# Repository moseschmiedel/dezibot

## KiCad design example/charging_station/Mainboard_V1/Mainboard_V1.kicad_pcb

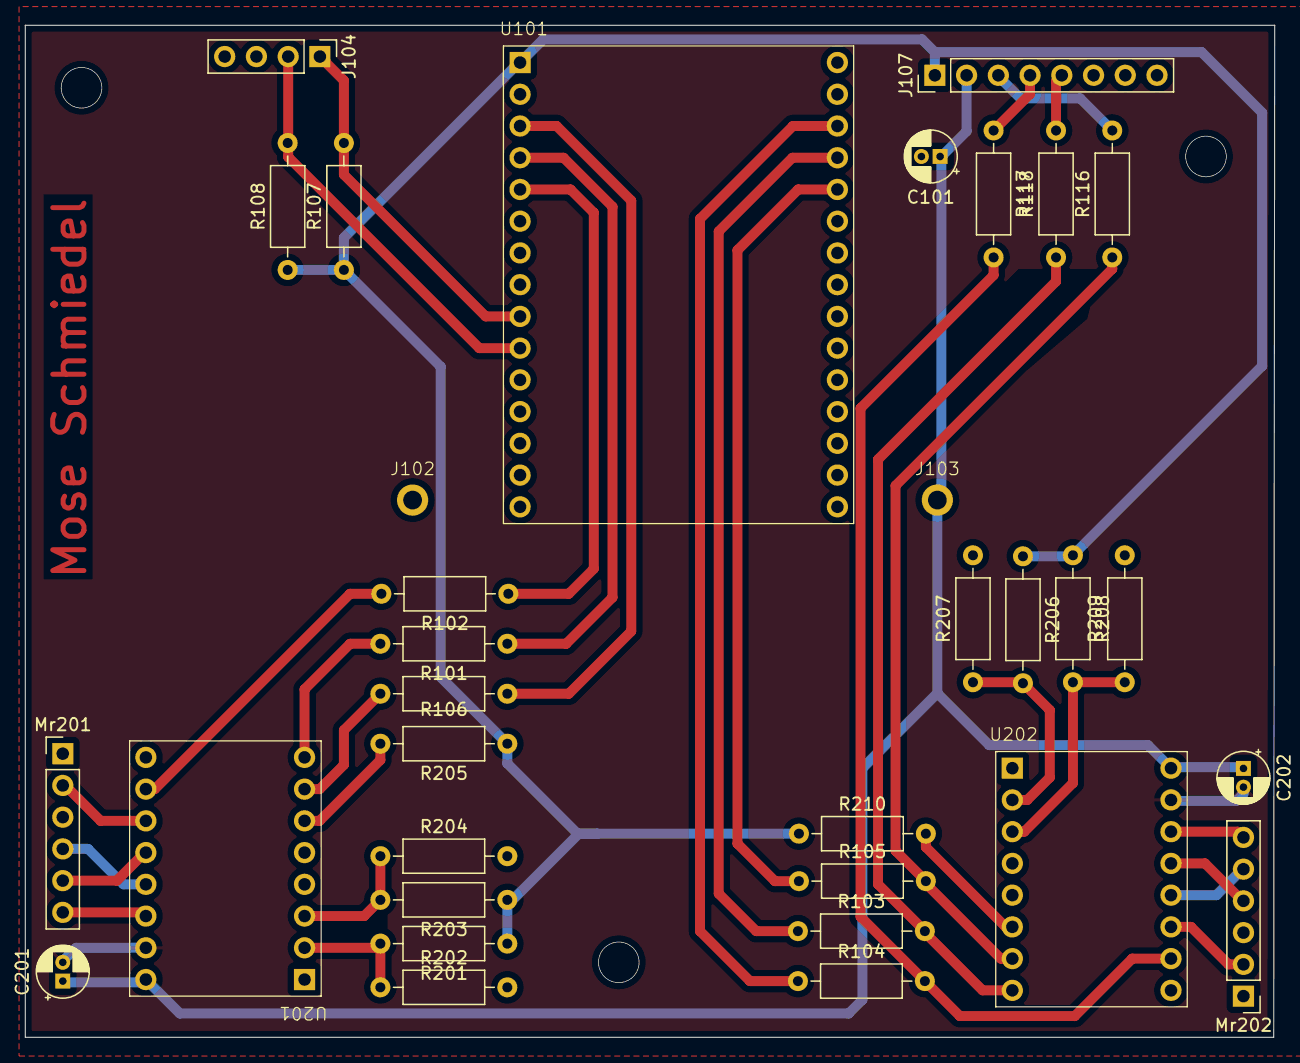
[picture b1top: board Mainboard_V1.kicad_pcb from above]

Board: 2 copper layers, 100.0 x 81.0 mm, 33 parts (0 on the bottom side), 34 nets.

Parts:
C101, C201, C202: 100uF; CP_Radial_D4.0mm_P1.50mm
J102, J103: PogoPin
J104: Conn_01x04_Pin; PinHeader_1x04_P2.54mm_Vertical
J107: Conn_01x08_Pin; PinHeader_1x08_P2.54mm_Vertical
Mr201, Mr202: Stepper_Motor_unipolar_6pin; PinHeader_1x06_P2.54mm_Vertical
R101, R102, R103, R104, R105, R106, R107, R108, R116, R117, R118, R201, R202, R203, R204, R205, R206, R207, R208, R209, R210: 1k; R_Axial_DIN0207_L6.3mm_D2.5mm_P10.16mm_Horizontal
U101: ESP32-WROOM-32; diymore-ESP32-WROOM-32-Devboard
U201, U202: DRV8834; Polulu_DRV8834

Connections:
/DIR_LEFT: R101.2, U201.8 (DIR)
/DIR_RIGHT: R103.2, R118.1, U202.8 (DIR)
/SCL: J104.2, R108.2, U101.10 (D19)
/SDA: J104.1, R107.2, U101.9 (D18)
/STEP_LEFT: R106.2, U201.7 (STEP)
/STEP_RIGHT: R105.2, R116.1, U202.7 (STEP)
/Stepper Motors/~SLEEP_LEFT: R205.2, U201.6 (~SLEEP)
/Stepper Motors/~SLEEP_RIGHT: R210.2, U202.6 (~SLEEP)
/~FAULT_LEFT: R102.2, U201.15 (~FAULT)
/~FAULT_RIGHT: R104.2, R117.2, U202.15 (~FAULT)
GND: C201.2, C202.2, U201.10 (GND), U202.10 (GND)
unnamed: J107.3, R116.2
unnamed: J107.4, R117.1
unnamed: J107.5, R118.2
unnamed: Mr201.5 (-), U201.13 (A1)
unnamed: R101.1, U101.4 (D2)
unnamed: R102.1, U101.5 (D4)
unnamed: R103.1, U101.19 (D12)
unnamed: R104.1, U101.18 (D13)
unnamed: R105.1, U101.20 (D14)
unnamed: R106.1, U101.3 (D15)
unnamed: Mr201.2, U201.14 (A2)
unnamed: Mr201.4, U201.12 (B1)
unnamed: Mr201.6, U201.11 (B2)
unnamed: R201.2, R202.1, U201.2 (M0)
unnamed: R203.2, R204.1, U201.3 (M1)
unnamed: Mr202.5 (-), U202.13 (A1)
unnamed: Mr202.2, U202.14 (A2)
unnamed: Mr202.4 (-), U202.12 (B1)
unnamed: Mr202.6, U202.11 (B2)
unnamed: R206.2, R207.1, U202.2 (M0)
unnamed: R208.2, R209.1, U202.3 (M1)
VBUS: C101.1, C201.1, C202.1, J103.1, J107.2, U201.9 (VMOT), U202.9 (VMOT)
VDD: J107.1, R107.1, R108.1, R201.1, R203.1, R205.1, R206.1, R208.1, R210.1, U101.1 (3V3)

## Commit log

2024-10-29 Add directory structure for charging_station firmware
2025-03-05 autocharge/#10-pick: specify `AbstractSet`
2025-03-05 autocharge/#10-pick: implement `AbstractSet` with `Fifo`
2025-03-05 autocharge/#10-pick: add `Master`
2025-03-05 autocharge/#10-pick: add `Slave`
2025-03-06 autocharge/#10-pick: add cs state `SLAVE_CHARGE`
2025-03-06 autocharge/#9-communication: specify api & request/response handling
2025-03-09 autocharge/#9-communication: slave steps...
2025-03-09 autocharge/#9-communication: master steps...
2025-03-10 Add KiCad project for charging station mainboard
2025-03-10 Add first stepper motor controller test
2025-03-10 Add charging station base structure in 3d model
2025-03-10 autocharge/#9-communication: add `ChargingStationState::ATTACHING_GEAR`
2025-03-10 autocharge/#9-state-management: refine state-management & add transitions
2025-03-11 autocharge/#15-communication: refine `Communication::sendMessage`
2025-03-11 autocharge/#15-communication: unicasting between slave/master
2025-03-11 autocharge/#15-communication: add `AbstractSet::get`
2025-03-11 autocharge/#15: handle incoming unicast messages
2025-03-11 autocharge/#15-communication: serial-print communication
2025-03-12 Improve mechanical design of charging station base
2025-03-17 autocharge/#15-communication
    * autocharge/#15-communication: refine `Communication::sendMessage`
    * autocharge/#15-communication: unicasting between slave/master
    * autocharge/#15-communication: add `AbstractSet::get`
    * autocharge/#15: handle incoming unicast messages
    * autocharge/#15-communication: serial-print communication
2025-03-17 fix printf
2025-03-17 cosmetics
2025-03-17 add dedicated global callback pointers
2025-03-17 remove old override
2025-03-17 inheritor singleton-like static members
2025-03-17 proper import dag
2025-03-17 autocharge/#15-communication: fix finicky errors
2025-03-18 Update 3d construction
2025-03-18 PCB changes
2025-03-18 remove `AbstractSet::getId`
2025-03-18 PCB updates
2025-03-20 Rework data structures for Master
2025-03-20 fix undefined ref `Master::master`
2025-03-20 fix undefined ref `Communication::unicast`
2025-03-20 add slave example
2025-03-20 move singleton-like init to constr
2025-03-20 examples step...
2025-03-20 Update PCB
2025-03-20 Pass slave as pointer
2025-03-20 PCB V1 first manufactured prototype
2025-03-24 First produced 3d prototype
2025-03-25 autocharge: add `Communication::getNodeId`
2025-03-25 autocharge: lambda consumers
2025-03-25 autocharge: derive public
2025-03-25 autocharge: linebreakl
2025-03-25 autocharge: equals instzead of ==
2025-03-25 autocharge: debug internal error
2025-03-26 autocharge: refine Slaves handling of enjoin-command
2025-03-30 autocharge: replace usage of `std::map::at` with `std::map::find` avoiding exception
2025-03-31 Add code for second motor driver
2025-03-31 autocharge: debug master state via leds
2025-03-31 autocharge: master demo
2025-03-31 autocharge: fix usage of pointers
2025-03-31 autocharge: remove doubler pointer and set current null after exit
2026-02-26 add setDutyCycle to InfraredLED
2026-02-26 Start with much higher frequency for LEDC PWM
2026-02-26 Add I2C communication with motor driver
